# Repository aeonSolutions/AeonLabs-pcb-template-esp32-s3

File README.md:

[PCB-Prototyping-Catalogue](https://github.com/aeonSolutions/PCB-Prototyping-Catalogue)  >>  [DIY & Maker](https://github.com/aeonSolutions/PCB-Prototyping-Catalogue/blob/main/DIY-Maker/README.md)   >> 
 [DIY & Makers PCBs essentials: modules / Shields](https://github.com/aeonSolutions/PCB-Prototyping-Catalogue/blob/main/PCB-Shields/README.md)  >>  ESP32 S3 

<p align="right">
 <a href="https://github-com.translate.goog/aeonSolutions/PCB-Prototyping-Catalogue/tree/main?_x_tr_sl=en&_x_tr_tl=pt&_x_tr_hl=en&_x_tr_pto=wapp">Change Language</a> <br>
Last update: 30-11-2023
</p>

# PCB template ESP32 S3

#
## Firmware Download 
one can use the PCB in the repository [AeonLabs-MCU-Burner-USB-to-UART-TTL](https://github.com/aeonSolutions/AeonLabs-MCU-Burner-USB-to-UART-TTL) to program the ESP32 WROOM32 MCU on this PCB.

#

<br>

*Don't forget to LIKE , SHARE and subscribe the free whatsApp group* and if you liked this PCB consider buying me a cup of coffee. Links below.

## Liked it ? Get a Free PCB for yourself
Send me your Device or hardware and i will design a custom PCB for it. Free of charge. Contact-me on WhatsApp or email for more info. 

## Q&A WhatsApp Group
If you have any Questions or simply  like this kind of projects and want to stay updated with the latest research ideas and prototypes during the day and week, join the WhatsApp Group
[A.I. Things](https://chat.whatsapp.com/FkNC7u83kuy2QRA5sqjBVg)

## Fully assembled PCB
Alternatively, and if you do not want to build a PCB by yourself and like to buy one, you can do it here:

<p align="center">
   
</p>

<br />
<br />

## Author

You can get in touch with me on my LinkedIn Profile:

#### Miguel Tomas

You can also follow my GitHub Profile to stay updated about my latest projects: 

<br>

### Be supportive of my dedication and work towards technology education and buy me a cup of coffee
The PCB Desgin Files i provide here for anyone to use are free. If you like this Smart Device or use it, please consider buying me a cup of coffee, a slice of pizza or a book to help me study, eat and think new PCB design files.

<p align+"left">

<br>

</p>

<br />

### Make a donation on Paypal
Make a donation on paypal and get a TAX refund*.

<br>

### Support all these open hardware projects and become a patreon  
Liked any of my PCB KiCad Designs? Help and Support my open work to all by becomming a LDAD Patreon.
In return I will give a free PCB design in KiCad to all patreon supporters. To learn more go to patreon.com. Link below.

#

### License

Before proceeding to download any of AeonLabs software solutions for open-source development and/or PCB hardware electronics development make sure you are choosing the right license for your project. See [AeonLabs Solutions for Open Hardware & Source Development](https://github.com/aeonSolutions/PCB-Prototyping-Catalogue/wiki/AeonLabs-Solutions-for-Open-Hardware-&-Source-Development) for more information.

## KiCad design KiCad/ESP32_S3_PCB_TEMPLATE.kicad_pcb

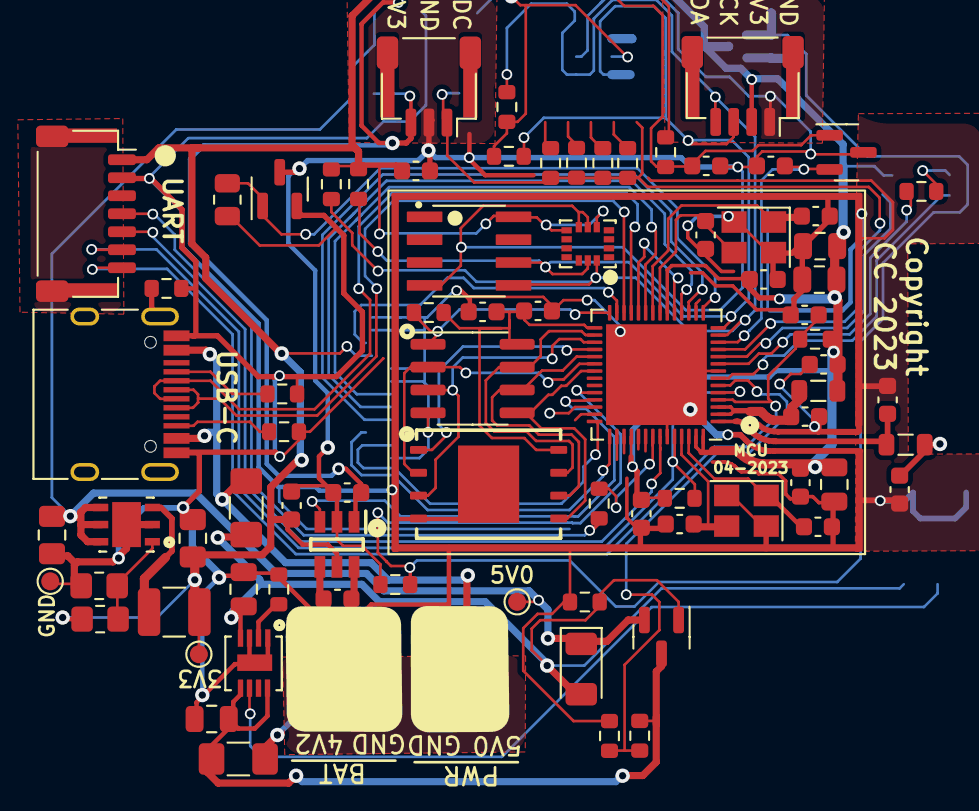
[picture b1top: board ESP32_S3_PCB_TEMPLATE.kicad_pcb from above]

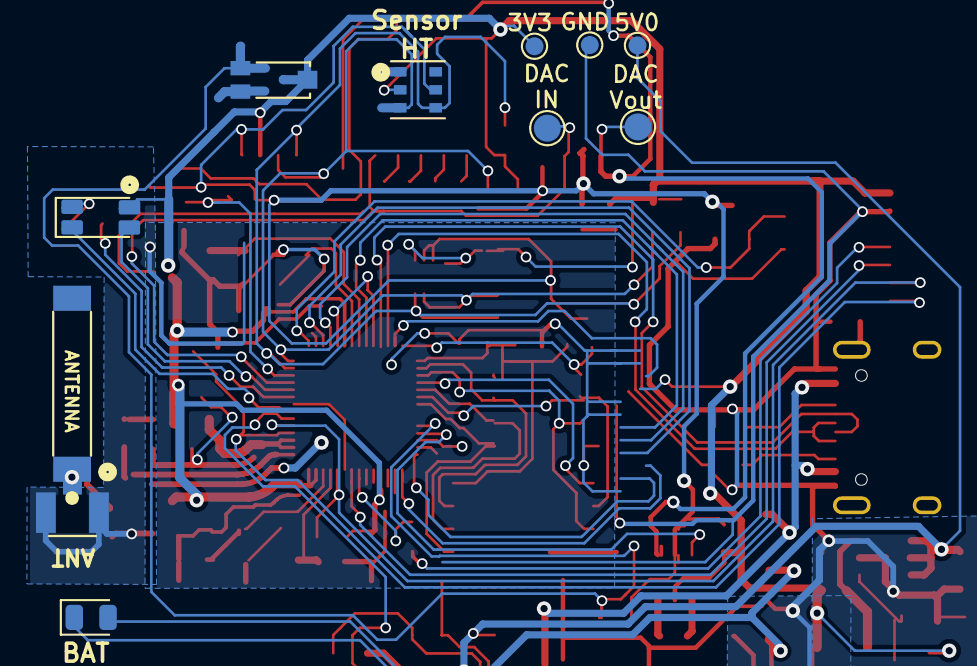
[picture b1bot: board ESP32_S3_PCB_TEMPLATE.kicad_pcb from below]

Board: 2 copper layers, 93 parts (12 on the bottom side), 53 nets.

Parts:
ATSHA_C1: 100nF; C_0603_1608Metric
AUR1: AUR9718x_DFN_3x3mm_6_pin; AUR9718 ST1S09 SON95P300X300X100-7N
AUR_C1: 22uF; C_0805_2012Metric_Pad1.18x1.45mm_HandSolder
AUR_C2: 4.7uF; C_0805_2012Metric_Pad1.18x1.45mm_HandSolder
AUR_R1: 75k; R_0805_2012Metric_Pad1.20x1.40mm_HandSolder
AUR_R2: 24k; R_0805_2012Metric_Pad1.20x1.40mm_HandSolder
AUR_l1: 3.3uF; L_1210_3225Metric
BAT_FUSE1: Polyfuse; Fuse_1206_3216Metric_Pad1.42x1.75mm_HandSolder
BAT_SENSE_R1, BAT_SENSE_R2: 100k; R_0603_1608Metric
CN3065_C2: 4.7uF; C_0805_2012Metric
CN3065_R1: 1K8; R_0603_1608Metric
CN3065_STDBY_LED1: LED; LED_0805_2012Metric
CN3965_C1: 22uF; C_0805_2012Metric
DIP_R1: 4k7; R_0603_1608Metric
DIP_R2: 1k; R_0603_1608Metric
DIP_R3: 20k; R_0603_1608Metric
DIP_R4: 200k; R_0603_1608Metric
DIP_R5: 2M; R_0603_1608Metric
DMP1045U_1: DMP1045U; SOT-23
DMP1045_R1: 10K; R_0603_1608Metric
DMP1045_SCHOT1: D_Schottky; D_1206_3216Metric
EPS1: ESP32-PSRAM_LY68L6400S; SOIC-8_3.9x4.9mm_P1.27mm
ESP32S1: ESP32-S3; QFN-56-1EP_7x7mm_P0.4mm_EP5.6x5.6mm
ESP32_SHIELD1: RFShield_OnePiece; ESP32-S3 GND Shield
ESP_FLASH1: W25Q128JVS; WSON8 FLASH SPI SON127P800X600X80-9N
E_DTR_R1: 10k; R_0603_1608Metric
E_LNA_ANT1: AN9520; 2.4ghZ WIFI ANTENNA AN9520_ANT2-SMD-9.5X2.1X1.0MM
E_LNA_ANT2: U.FL-R-SMT(01); RF Antenna IPEX SMD PCB HRS_U.FL-R-SMT(01)
E_LNA_C1, E_LNA_C2: 2.7pF; C_0603_1608Metric
E_LNA_l1: 1.8nH 5%; L_0805_2012Metric
E_RTS_C1: 100nF; C_0603_1608Metric
E_RTS_R1: 10k; R_0603_1608Metric
E_SPI_C1: 1uF 10% 50V; C_0603_1608Metric
E_SPI_C2: 100nF 10% 16V; C_0603_1608Metric
E_UART_TX_1: 499R; R_0603_1608Metric
E_VDDA_C1: 100nF; C_0603_1608Metric
E_VDDA_C2: 1uF 10% 50V; C_0805_2012Metric
E_VDD_3_C1, E_VDD_3_C2: 10uF 20% 6.3V; C_0805_2012Metric
E_VDD_3_C3, E_VDD_3_C4: 100nF 10% 16V; C_0603_1608Metric
E_VDD_CPU_C1: 100nF 10% 16V; C_0603_1608Metric
E_VDD_L1: 12nH 5%; L_0805_2012Metric
E_VDD_RTC_C1: 100nF 10% 16V; C_0603_1608Metric
E_XTAL32_1: 32.768Mhz 22pF+-10PPM; Crystal_SMD_3225-4Pin_3.2x2.5mm
E_XTAL32_C1, E_XTAL32_C2, E_XTAL40_C1, E_XTAL40_C2: 22pF 5% 50V; C_0603_1608Metric
E_XTAL40_1: 40Mhz 22pF+-10PPM; Crystal_SMD_3225-4Pin_3.2x2.5mm
ExtSW1: Conn_01x03_Female; JST_SH_SM03B-SRSS-TB_1x03-1MP_P1.00mm_Horizontal
ExtSWBAT_PLUG2: Conn_01x03_Female; JST_SH_SM03B-SRSS-TB_1x03-1MP_P1.00mm_Horizontal
HX1: HX4002; HX4002 SOT95 P280X125-6N
HX_C1, HX_C2, HX_C3: 2.2uF; C_0603_1608Metric
I2C_PLUG1: I2C6; JST_SH_SM04B-SRSS-TB_1x04-1MP_P1.00mm_Horizontal
I2C_SCL_R1, I2C_SDA_R1: 10k; R_0603_1608Metric
IMR1, IMR2: 10K; R_0603_1608Metric
IMU1: LSM6DS3; LSM6DS3 Motion Sensor PQFN50P300X250X86-14N
J1: TYPE-C-31-M-12; USB_C_Receptacle_HRO_TYPE-C-31-M-12
JICSP1: Conn_01x07_Socket; JST_SH_SM07B-SRSS-TB_1x07-1MP_P1.00mm_Horizontal
LED1: LED_GBRC; LED_1206_3210_RGB_Metric
LR1: 330R; R_0603_1608Metric
MTRR1: 10k; R_0805_2012Metric
MTRT1: NPN; SOT-23
PSRAM_R1: 100K; R_0603_1608Metric
PWR_FUSE1: Polyfuse; Fuse_1206_3216Metric_Pad1.42x1.75mm_HandSolder
PWR_PLUG1: Screw_Terminal_01x02; JST_SH_SM02B-SRSS-TB_1x02-1MP_P1.00mm_Horizontal
Sign-PbFree: LOGO_PBFREE
Sign-RecycleBin: LOGO_RECYCLEBIN_1
Sign-RoHS: LOGO_ROHS_1
TMPR1: 10K; R_0603_1608Metric
TP1, TP1#2: VIN; TestPoint_Pad_D1.0mm
TP2, TP2#2: VOut; TestPoint_Pad_D1.0mm
TP3, TP3#2: GND; TestPoint_Pad_D1.0mm
U1: MCP1525-TT; SOT-23
U2: ATSHA204A-MAHDA-T; ATSHA204A Auth SOIC8
U3: Battery_charger_CN3065_QFN8; QFN8 3.1x2.9mm QFNn-8 3x3 SON80P400X400X100-9N
U4: AHT20; AHT20 HT Sensor PSON100P300X300X110-6N
U6: TEMT6000; TEMT6000-SEN
USB_PLUG_R1, USB_PLUG_R3: 5k1; R_0603_1608Metric
USB_PLYG_R2: 150K; R_0603_1608Metric
VOLTAGE_REF_C1, VOLTAGE_REF_C2: 100nF; C_0603_1608Metric

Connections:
3V3: ATSHA_C1.2, AUR_C1.1, AUR_R1.1, AUR_l1.1, ESP32S1.20 (VDD3P3_RTC), ESP32S1.46 (VDD3P3_CPU), ESP32S1.55 (VDDA), ESP32S1.56 (VDDA), E_DTR_R1.1, E_RTS_R1.1, E_VDDA_C1.2, E_VDDA_C2.2, E_VDD_3_C1.1, E_VDD_3_C2.1, E_VDD_3_C3.1, E_VDD_CPU_C1.1, E_VDD_L1.1, E_VDD_RTC_C1.1, HX1.5 (VIN), HX_C3.2, I2C_PLUG1.2, I2C_SCL_R1.1, I2C_SDA_R1.2, IMR1.1, IMR2.1, IMU1.5 (VDDIO), IMU1.8 (VDD), JICSP1.1, LED1.4 (K), TP2.1, TP2#2.1, U2.8 (VCC), U4.2 (VDD), U6.COLLECTOR
3V3_PLUG: DIP_R1.2, ExtSW1.3, HX1.1 (VOUT), HX_C1.1, U1.1 (Vin), VOLTAGE_REF_C1.2
ADC_IN_IO04: DIP_R2.1, DIP_R3.1, DIP_R4.1, DIP_R5.1, ESP32S1.11 (GPIO6/ADC1_CH5), ExtSW1.1
BAT_SENSE_IO21: BAT_SENSE_R1.1, BAT_SENSE_R2.2, ESP32S1.6 (GPIO1/ADC1_CH0)
CHIP_EN: ESP32S1.4 (CHIP_PU/RESET), E_RTS_C1.2, E_RTS_R1.2, JICSP1.7
DAC_CALIBRATION: ESP32S1.19 (GPIO14/ADC2_CH3), ESP32S1.24 (GPIO18/ADC2_CH7/DAC_1)
ESP_GPIO0_BOOT-DTR: ESP32S1.5 (GPIO0/BOOT), ESP32S1.52 (GPIO46), E_DTR_R1.2, JICSP1.6
GND: AUR1.2 (GND), AUR1.7 (GND), AUR_C1.2, AUR_C2.2, AUR_R2.2, BAT_SENSE_R1.2, CN3065_C2.1, CN3065_R1.1, CN3965_C1.1, DMP1045_R1.2, EPS1.4 (VSS), ESP32S1.8 (GPIO3/ADC1_CH2), ESP32S1.51 (GPIO45), ESP32S1.57 (GND), ESP32_SHIELD1.1 (Shield), ESP_FLASH1.4 (GND), ESP_FLASH1.9 (GND), E_LNA_ANT2.1 (GND), E_LNA_ANT2.2 (GND), E_LNA_C1.2, E_LNA_C2.2, E_RTS_C1.1, E_SPI_C1.2, E_SPI_C2.2, E_VDDA_C1.1, E_VDDA_C2.1, E_VDD_3_C1.2, E_VDD_3_C2.2, E_VDD_3_C3.2, E_VDD_3_C4.2, E_VDD_CPU_C1.2, E_VDD_RTC_C1.2, E_XTAL32_1.2, E_XTAL32_1.4, E_XTAL32_C1.2, E_XTAL32_C2.2, E_XTAL40_1.2, E_XTAL40_1.4, E_XTAL40_C1.2, E_XTAL40_C2.2, ExtSWBAT_PLUG2.3, J1.B1, J1.B12, JICSP1.2, MTRR1.1, MTRT1.2, PWR_PLUG1.1, TP3.1, TP3#2.1, U3.1 (V_Temp), U3.3 (GND), U3.9 (GND), USB_PLUG_R1.2, USB_PLUG_R3.2, USB_PLYG_R2.2
GNDD: ATSHA_C1.1, ExtSW1.2, ExtSW1.MP, ExtSWBAT_PLUG2.MP, HX1.2 (GND), HX_C1.2, HX_C3.1, I2C_PLUG1.1, I2C_PLUG1.MP, IMU1.6 (GND), IMU1.7 (GND), JICSP1.MP, MTRT1.3, PWR_PLUG1.MP, TMPR1.1, U1.3 (Vss), U2.4 (GND), U4.5 (GND), VOLTAGE_REF_C1.1, VOLTAGE_REF_C2.1
GPIO8_I2C_SDA: ESP32S1.13 (GPIO8/ADC1_CH7), I2C_PLUG1.4, I2C_SDA_R1.1, IMR1.2, IMU1.14 (SDA), U2.5 (SDA), U4.4 (SDA)
GPIO9_I2C_SCL: ESP32S1.14 (GPIO9/ADC1_CH8), I2C_PLUG1.3, I2C_SCL_R1.2, IMR2.2, IMU1.13 (SCL), U2.6 (SCL), U4.3 (SCL)
LED_B_IO05: ESP32S1.10 (GPIO5/ADC1_CH4), LED1.2 (BA)
LED_G_IO02: ESP32S1.7 (GPIO2/ADC1_CH1), LED1.1 (GA)
LED_R_IO04: ESP32S1.9 (GPIO4/ADC1_CH3), LR1.1
unnamed: AUR1.1 (FB), AUR_R1.2, AUR_R2.1
unnamed: AUR1.3 (SW), AUR_l1.2
unnamed: ESP32S1.21 (GPIO15/ADC2_CH4/XTAL_32K_P), E_XTAL32_1.3, E_XTAL32_C1.1
unnamed: ESP32S1.22 (GPIO16/ADC2_CH5/XTAL_32K_N), E_XTAL32_1.1, E_XTAL32_C2.1
unnamed: ESP32S1.1 (LNA_IN/RF), E_LNA_C2.1, E_LNA_l1.2
unnamed: ESP32S1.49 (U0TXD/PROG/GPIO43), E_UART_TX_1.2
unnamed: ESP32S1.2 (VDD3P3), ESP32S1.3 (VDD3P3), E_VDD_3_C4.1, E_VDD_L1.2
unnamed: ESP32S1.53 (XTAL_N), E_XTAL40_1.3, E_XTAL40_C2.1
unnamed: ESP32S1.54 (XTAL_P), E_XTAL40_1.1, E_XTAL40_C1.1
unnamed: E_LNA_ANT1.1, E_LNA_ANT2.3 (SIG), E_LNA_C1.1, E_LNA_l1.1
unnamed: HX1.6 (C+), HX_C2.1
unnamed: HX1.4 (C-), HX_C2.2
unnamed: J1.A5 (CC1), USB_PLUG_R3.1
unnamed: J1.B5 (CC2), USB_PLUG_R1.1
unnamed: J1.S1 (SHIELD), USB_PLYG_R2.1
unnamed: LED1.3 (RA), LR1.2
unnamed: CN3065_R1.2, U3.2 (I_SET)
PERIPHERALS_PWR_EN_IO10: ESP32S1.15 (GPIO10/ADC1_CH9), MTRR1.2, MTRT1.1
PLUG_PWR_3V3_EN_IO38: ESP32S1.39 (GPIO34), HX1.3 (EN)
RXD0: ESP32S1.50 (U0RXD/PROG/GPIO44), JICSP1.5
SPICLK: EPS1.6 (SCLK), ESP32S1.33 (SPICLK/GPIO30), ESP_FLASH1.6 (CLK)
SPICS0: ESP32S1.32 (SPICS0/GPIO29), ESP_FLASH1.1 (~CS)
SPICS1: EPS1.1 (~CE), ESP32S1.28 (SPI_CS1/GPIO26), PSRAM_R1.1
SPID: EPS1.5 (SiO0), ESP32S1.35 (SPID/GPIO32), ESP_FLASH1.5 (DI(IO0))
SPIHD: EPS1.7 (SIO3), ESP32S1.30 (SPIHD/GPIO27), ESP_FLASH1.7 (IO3)
SPIQ: EPS1.2 (SIO1), ESP32S1.34 (SPIQ/GPIO31), ESP_FLASH1.2 (DO(IO1))
SPIWP: EPS1.3 (SIO2), ESP32S1.31 (SPIWP/GPIO28), ESP_FLASH1.3 (IO2)
STDBY_LED_G: CN3065_STDBY_LED1.1 (K), U3.6 (LED_DONE)
TEMT6000_IO33: ESP32S1.38 (GPIO33), TMPR1.2, U6.EMITTER
TXD0: E_UART_TX_1.1, JICSP1.4
USB_5V0: CN3065_STDBY_LED1.2 (A), CN3965_C1.2, DMP1045U_1.1, DMP1045_R1.1, DMP1045_SCHOT1.2 (A), PWR_FUSE1.1, U3.4 (VIN)
USB_5V0F: J1.A4, J1.A9, PWR_FUSE1.2, PWR_PLUG1.2
USB_D+: ESP32S1.26 (GPIO20/USB_D+/ADC2_CH9), J1.A6 (DP1), J1.B6 (DP2)
USB_D-: ESP32S1.25 (GPIO19/USB_D-/ADC2_CH8), J1.A7 (DN1), J1.B7 (DN2)
VDD_SPI: EPS1.8 (VCC), ESP32S1.29 (VDD_SPI), ESP_FLASH1.8 (VCC), E_SPI_C1.1, E_SPI_C2.1, PSRAM_R1.2
VIN: AUR1.4 (VIN_SW), AUR1.5 (VIN_A), AUR1.6 (EN), AUR_C2.1, DMP1045U_1.2, DMP1045_SCHOT1.1 (K), TP1.1, TP1#2.1
VIN_BAT: BAT_FUSE1.1, BAT_SENSE_R2.1, CN3065_C2.2, DMP1045U_1.3, U3.5 (BAT+), U3.8 (FB)
VIN_BATF: BAT_FUSE1.2, ExtSWBAT_PLUG2.1
VOLTAGE_REF_IO07: ESP32S1.12 (GPIO7/ADC1_CH6), U1.2 (Vout), VOLTAGE_REF_C2.2
